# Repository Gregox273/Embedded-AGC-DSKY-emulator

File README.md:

# Embedded-AGC-DSKY-emulator
Apollo Block II AGC + DSKY emulator based on the virtualagc project (https://github.com/virtualagc/virtualagc).
The system is based on an STM32 32-bit ARM Cortex MCU, with custom PCB layout to match the position of buttons and lamps 
on the original DSKY.

### Repository Layout
* **agg-kicad:** submodule by Adam Greig containing useful KiCAD libraries, footprints and scripts.
* **binary_transcoder:** simple C program to rearrange binary output of the yaYUL assembler (see **virtualagc** 
submodule) into the order required for yaAGC emulator (also contained within **virtualagc**). Note that a pre-transcoded
binary file for Luminary099 is provided in the **firmware** directory.
* **ChibiOS:** ChibiOS RTOS submodule, developed by Giovanni Di Sirio.
* **firmware:** directory containing project source code.
* **gen-board.h:** submodule containing Python tool for generating ChibiOS 'board.h' header from a YAML file.
* **pcb:** directory containing project schematics and PCB design:
    * **agc-dsky:** KiCAD schematic and PCB files.
    * **agc-dsky.pretty:** Various component footprints.
    * **lib:** Various schematic symbols.
* **virtualagc:** Virtual Apollo Guidance Computer submodule. Contents include yaYUL (Apollo language assembler) and 
yaAGC (Apollo Guidance Computer emulator).

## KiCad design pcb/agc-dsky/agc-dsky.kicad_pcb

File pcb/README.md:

# Hardware Notes
* STM32F072RBT6 48MHz microcontroller based on ARM Cortex-M0 core. 48MHz appears to be too slow to run the emulator and 
DSKY in realtime...
* MPU9250 IMU present on SPI2 bus (firmware can communicate with device but it has not yet been incorporated into the 
AGC emulation).
* Powered via Micro USB (<500mA current consumption at any time, so can be powered from e.g. a USB port on a computer).
* Microcontroller can be flashed over USB using DFU, or via Serial Wire Debug (SWD).
* TPS62132 switching regulator (5V USB to 3.3V) - high efficiency reduces overall current consumption.
* MCP23S08 SPI I/O expanders used to drive 7 segment displays in a multiplexed array.
  * Three displays are illuminated at a time, striking a balance between brightness and current consumption.
* Push buttons are multiplexed in a key matrix to reduce I/O pin usage.
* WS2812B LEDs arranged in a chain, allowing them to be driven from a single output pin. Each LED internally handles PWM
for red, green and blue channels.
  * Todo: drive LEDs using DMA instead of blocking the processor. This technique appears to be better documented on 
  STM32F3 and STM32F4 microcontrollers.
* UART port exposed (2.54mm header) to allow for future modifications/experimentation.

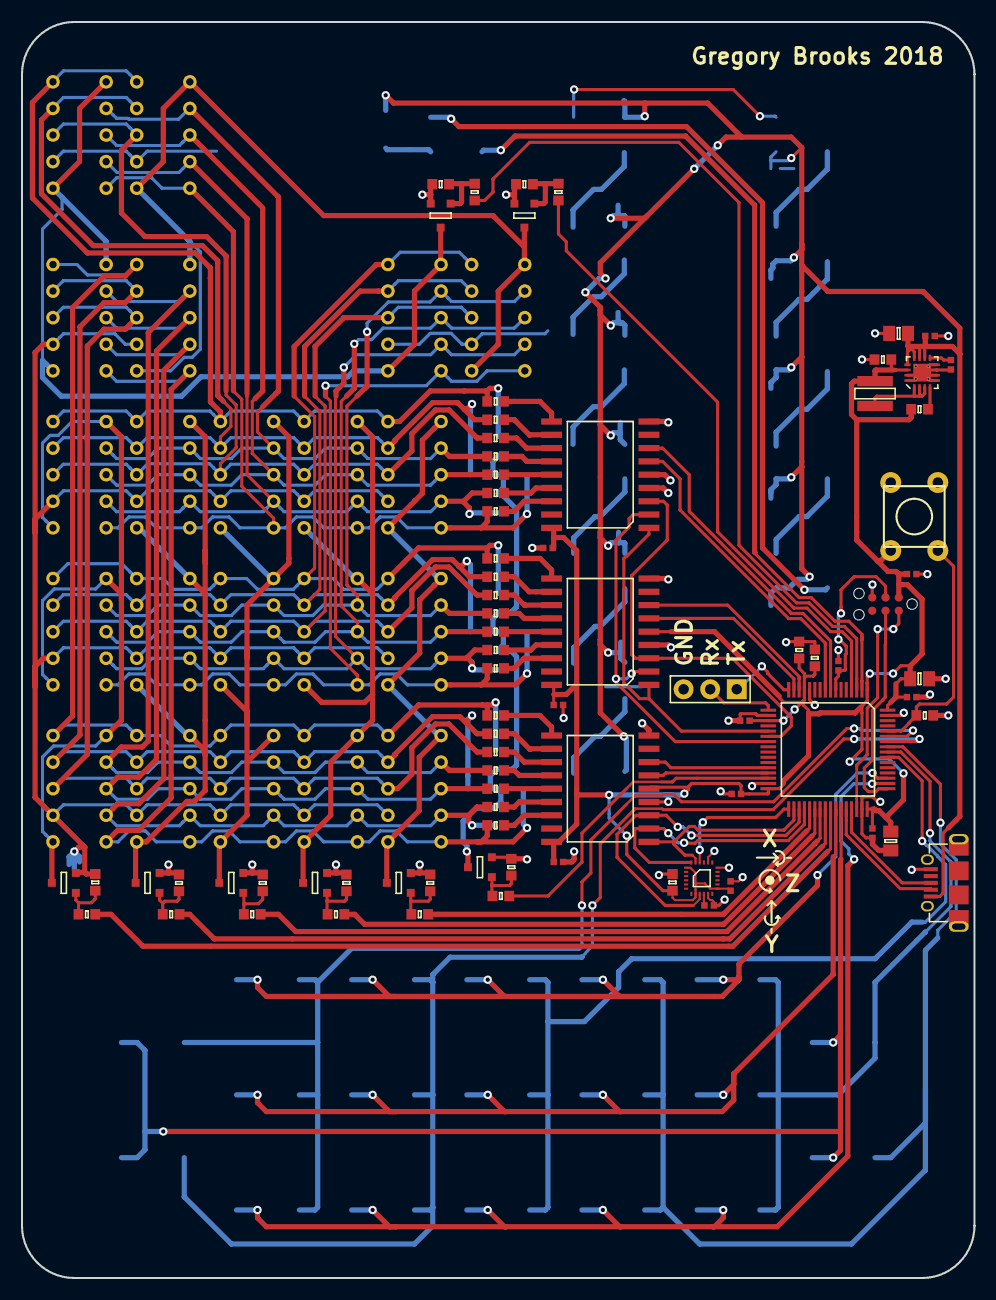
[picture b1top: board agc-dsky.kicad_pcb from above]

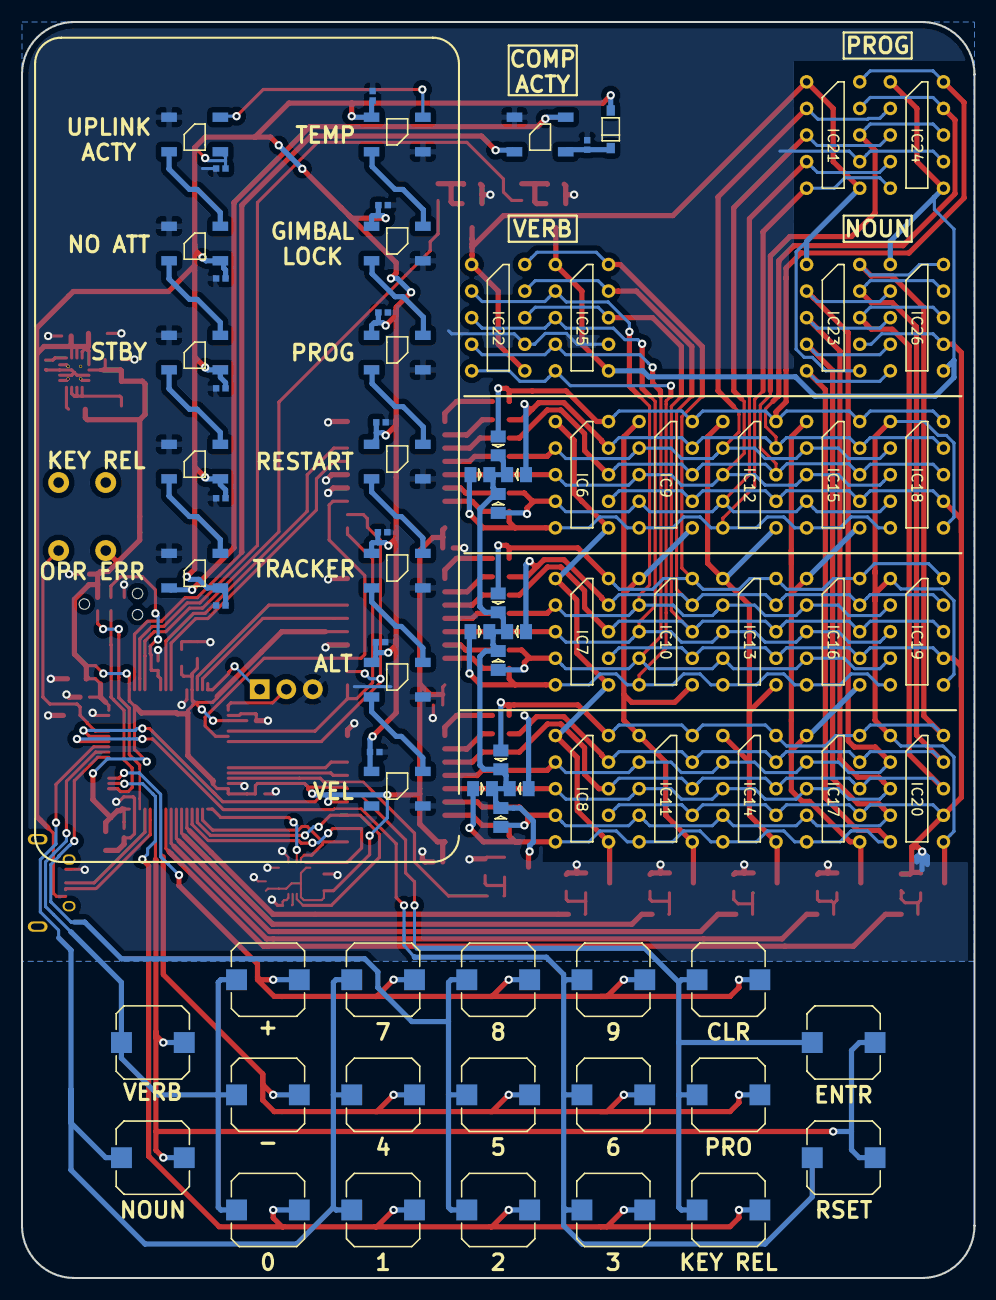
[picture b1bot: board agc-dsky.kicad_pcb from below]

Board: 2 copper layers, 91.0 x 120.0 mm, 157 parts (79 on the bottom side), 117 nets.

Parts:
C1: 10uF; 0805
C2, C4, C7, C10, C11, C13, C14, C15, C16, C17, C18, C19, C20, C21, C22, C23, C24, C25, C26, C27, C28, C29, C30, C31, C33: 100nF; 0402
C3: 3.3nF; 0402
C5: 22uF; 0603
C6, C8: 4.7uF; 0805
C9: 1uF; 0603
C12, C32: 10nF; 0603
D1, D2, D3, D4, D5, D6, D7, D8, D9, D10, D11, D12: LED; 0805-LED
D13: MMSD4148T1G; SOD-123
IC1: TPS62132; QFN-16-EP-TI
IC2: STM32F072RBT6; LQFP-64
IC3, IC4, IC5: MCP23S08; SOIC-18-W
IC6, IC7, IC8, IC9, IC10, IC11, IC12, IC13, IC14, IC15, IC16, IC17, IC18, IC19, IC20, IC21, IC22, IC23, IC24, IC25, IC26: LDS-3161AX
IC27, IC28, IC29, IC30, IC31, IC32, IC33, IC34, IC35, IC36, IC37, IC38, IC39: WS2812B
IC40: MPU-9250; QFN-24-MPU9250
J1: MICROUSB; MICROUSB_MOLEX_47589-0001
J2: CONN_01x03; SIL-254P-03
L1: 2.2uH; XFL4020
P1: SWD_TC; TC2030-NL
Q1, Q2, Q3, Q4, Q5, Q6, Q7, Q8: FDN327N; supersot-3
R1, R2: 100k; 0603
R3, R4, R5, R6, R7, R8, R9, R10, R11, R12, R13, R14, R15, R16, R17, R18, R19, R20, R21, R22, R23, R24, R26, R28, R30, R32, R34, R36, R38: 100; 0603
R25, R27, R29, R31, R33, R35, R37, R39: 1M; 0603
SW1, SW2, SW3, SW4, SW5, SW6, SW7, SW8, SW10, SW11, SW12, SW13, SW14, SW15, SW16, SW17, SW18, SW19, SW20: SKPMAME010; SKPM
SW9: SKHHALA010; MOM_SWITCH

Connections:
3v3: C4.1, C5.1, C6.1, C7.1, C8.1, C9.1, C10.1, C11.1, C12.1, C13.1, C15.1, C16.1, C17.1, C31.2, C32.1, IC1.14, IC2.1, IC2.13, IC2.19, IC2.32, IC2.48, IC2.64, IC3.18, IC4.5, IC4.18, IC5.4, IC5.5, IC5.18, IC40.1, IC40.8, IC40.13, L1.2, P1.1, R1.1, SW9.2
5v: C1.1, C2.1, C18.1, C19.1, C20.1, C21.1, C22.1, C24.1, C25.1, C26.1, C27.1, C28.1, C29.1, C30.1, D13.2, IC1.10, IC1.11, IC1.12, IC1.13, IC28.1, IC29.1, IC30.1, IC31.1, IC32.1, IC33.1, IC34.1, IC35.1, IC36.1, IC37.1, IC38.1, IC39.1, J1.1
/7-segs/A1: D10.2, IC6.10, IC9.10, IC12.10, IC15.10, IC18.10, IC21.10, IC24.10, R15.2
/7-segs/A2: D11.2, IC7.10, IC10.10, IC13.10, IC16.10, IC19.10, IC22.10, IC25.10, R18.2
/7-segs/A3: D12.2, IC8.10, IC11.10, IC14.10, IC17.10, IC20.10, IC23.10, IC26.10, R21.2
/7-segs/B1: D7.2, IC6.9, IC9.9, IC12.9, IC15.9, IC18.9, IC21.9, IC24.9, R9.2
/7-segs/B2: D8.2, IC7.9, IC10.9, IC13.9, IC16.9, IC19.9, IC22.9, IC25.9, R11.2
/7-segs/B3: D9.2, IC8.9, IC11.9, IC14.9, IC17.9, IC20.9, IC23.9, IC26.9, R13.2
/7-segs/C1: IC6.8, IC9.8, IC12.8, IC15.8, IC18.8, IC21.8, IC24.8, R3.2
/7-segs/C2: IC7.8, IC10.8, IC13.8, IC16.8, IC19.8, IC22.8, IC25.8, R5.2
/7-segs/C3: IC8.8, IC11.8, IC14.8, IC17.8, IC20.8, IC23.8, IC26.8, R7.2
/7-segs/D1: D4.2, IC6.5, IC9.5, IC12.5, IC15.5, IC18.5, IC21.5, IC24.5, R17.2
/7-segs/D2: D5.2, IC7.5, IC10.5, IC13.5, IC16.5, IC19.5, IC22.5, IC25.5, R20.2
/7-segs/D3: D6.2, IC8.5, IC11.5, IC14.5, IC17.5, IC20.5, IC23.5, IC26.5, R23.2
/7-segs/E1: D1.2, IC6.4, IC9.4, IC12.4, IC15.4, IC18.4, IC21.4, IC24.4, R4.2
/7-segs/E2: D2.2, IC7.4, IC10.4, IC13.4, IC16.4, IC19.4, IC22.4, IC25.4, R6.2
/7-segs/E3: D3.2, IC8.4, IC11.4, IC14.4, IC17.4, IC20.4, IC23.4, IC26.4, R8.2
/7-segs/F1: IC6.2, IC9.2, IC12.2, IC15.2, IC18.2, IC21.2, IC24.2, R16.2
/7-segs/F2: IC7.2, IC10.2, IC13.2, IC16.2, IC19.2, IC22.2, IC25.2, R19.2
/7-segs/F3: IC8.2, IC11.2, IC14.2, IC17.2, IC20.2, IC23.2, IC26.2, R22.2
/7-segs/G1: IC6.3, IC9.3, IC12.3, IC15.3, IC18.3, IC21.3, IC24.3, R10.2
/7-segs/G2: IC7.3, IC10.3, IC13.3, IC16.3, IC19.3, IC22.3, IC25.3, R12.2
/7-segs/G3: IC8.3, IC11.3, IC14.3, IC17.3, IC20.3, IC23.3, IC26.3, R14.2
/BC1: IC2.56, SW1.1, SW2.1, SW3.1, SW4.1
/BC2: IC2.57, SW5.1, SW6.1, SW7.1, SW8.1
/BC3: IC2.55, SW10.1, SW11.1, SW12.1
/BC4: IC2.58, SW14.1, SW15.1, SW16.1, SW17.1
/BC5: IC2.59, SW13.1, SW18.1, SW19.1, SW20.1
/BR1: IC2.51, SW1.2, SW5.2, SW10.2, SW14.2, SW18.2
/BR2: IC2.42, SW2.2, SW6.2, SW11.2, SW15.2, SW19.2
/BR3: IC2.50, SW3.2, SW7.2, SW12.2, SW16.2, SW20.2
/BR4: IC2.43, SW4.2, SW8.2, SW13.2, SW17.2
/Co1: IC2.37, R24.1
/Co2: IC2.38, R26.1
/Co3: IC2.39, R28.1
/Co4: IC2.40, R30.1
/Co5: IC2.41, R32.1
/Co6: IC2.4, R34.1
/Co7: IC2.3, R36.1
/Co8: IC2.30, R38.1
/LED_DIN: IC2.2, IC27.4
/NCS_1: IC2.8, IC3.7
/NCS_2: IC2.14, IC4.7
/NCS_3: IC2.28, IC5.7
/NCS_MPU: IC2.33, IC40.22
/NRST: C14.1, IC2.7, P1.3
/NRST_1: IC2.9, IC3.6
/NRST_2: IC2.15, IC4.6
/NRST_3: IC2.29, IC5.6
/SPI1_SCK: IC2.21, IC3.1, IC4.1
/SPI1_SI: IC2.23, IC3.2, IC4.2
/SPI1_SO: IC2.22, IC3.3, IC4.3
/SPI2_SCK: IC2.34, IC5.1, IC40.23
/SPI2_SI: IC2.36, IC5.2, IC40.24
/SPI2_SO: IC2.35, IC5.3, IC40.9
/SWDCLK: IC2.49, P1.4
/SWDIO: IC2.46, P1.2
GND: C1.2, C2.2, C3.1, C4.2, C5.2, C6.2, C7.2, C8.2, C9.2, C10.2, C11.2, C12.2, C13.2, C14.2, C15.2, C16.2, C17.2, C18.2, C19.2, C20.2, C21.2, C22.2, C23.2, C24.2, C25.2, C26.2, C27.2, C28.2, C29.2, C30.2, C31.1, C32.2, C33.2, IC1.5, IC1.6, IC1.7, IC1.8, IC1.15, IC1.16, IC1.EP, IC2.12, IC2.18, IC2.31, IC2.47, IC2.63, IC3.4, IC3.5, IC3.9, IC4.4, IC4.9, IC5.9, IC6.7, IC7.7, IC8.7, IC9.7, IC10.7, IC11.7, IC12.7, IC13.7, IC14.7, IC15.7, IC16.7, IC17.7, IC18.7, IC19.7, IC20.7, IC21.7, IC22.7, IC23.7, IC24.7, IC25.7, IC26.7, IC27.3, IC28.3, IC29.3, IC30.3, IC31.3, IC32.3, IC33.3, IC34.3, IC35.3, IC36.3, IC37.3, IC38.3, IC39.3, IC40.11, IC40.18, IC40.20, J1.5, J2.3, P1.5, Q1.S, Q2.S, Q3.S, Q4.S, Q5.S, Q6.S, Q7.S, Q8.S, R2.2, R25.2, R27.2, R29.2, R31.2, R33.2, R35.2, R37.2, R39.2
unnamed: C3.2, IC1.9
unnamed: C23.1, D13.1, IC27.1
unnamed: C33.1, IC40.10
unnamed: D1.1, D2.1, D3.1, D4.1, D5.1, D6.1, D7.1, D8.1, D9.1, D10.1, D11.1, D12.1, Q8.D
unnamed: IC1.1, IC1.2, IC1.3, L1.1
unnamed: IC1.4, R1.2
unnamed: IC2.16, J2.1
unnamed: IC2.17, J2.2
unnamed: IC2.44, J1.2
unnamed: IC2.45, J1.3
unnamed: IC2.60, R2.1, SW9.1
unnamed: IC3.10, R15.1
unnamed: IC3.11, R9.1
unnamed: IC3.12, R3.1
unnamed: IC3.13, R16.1
unnamed: IC3.14, R10.1
unnamed: IC3.15, R4.1
unnamed: IC3.16, R17.1
unnamed: IC4.10, R18.1
unnamed: IC4.11, R11.1
unnamed: IC4.12, R5.1
unnamed: IC4.13, R19.1
unnamed: IC4.14, R12.1
unnamed: IC4.15, R6.1
unnamed: IC4.16, R20.1
unnamed: IC5.10, R21.1
unnamed: IC5.11, R13.1
unnamed: IC5.12, R7.1
unnamed: IC5.13, R22.1
unnamed: IC5.14, R14.1
unnamed: IC5.15, R8.1
unnamed: IC5.16, R23.1
unnamed: IC6.1, IC6.6, IC7.1, IC7.6, IC8.1, IC8.6, Q1.D
unnamed: IC9.1, IC9.6, IC10.1, IC10.6, IC11.1, IC11.6, Q2.D
unnamed: IC12.1, IC12.6, IC13.1, IC13.6, IC14.1, IC14.6, Q3.D
unnamed: IC15.1, IC15.6, IC16.1, IC16.6, IC17.1, IC17.6, Q4.D
unnamed: IC18.1, IC18.6, IC19.1, IC19.6, IC20.1, IC20.6, Q5.D
unnamed: IC21.1, IC21.6, IC22.1, IC22.6, IC23.1, IC23.6, Q6.D
unnamed: IC24.1, IC24.6, IC25.1, IC25.6, IC26.1, IC26.6, Q7.D
unnamed: IC27.2, IC28.4
unnamed: IC28.2, IC29.4
unnamed: IC29.2, IC30.4
unnamed: IC30.2, IC31.4
unnamed: IC31.2, IC32.4
unnamed: IC32.2, IC33.4
unnamed: IC33.2, IC34.4
unnamed: IC34.2, IC35.4
unnamed: IC35.2, IC36.4
unnamed: IC36.2, IC37.4
unnamed: IC37.2, IC38.4
unnamed: IC38.2, IC39.4
unnamed: Q1.G, R24.2, R25.1
unnamed: Q2.G, R26.2, R27.1
unnamed: Q3.G, R28.2, R29.1
unnamed: Q4.G, R30.2, R31.1
unnamed: Q5.G, R32.2, R33.1
unnamed: Q6.G, R34.2, R35.1
unnamed: Q7.G, R36.2, R37.1
unnamed: Q8.G, R38.2, R39.1

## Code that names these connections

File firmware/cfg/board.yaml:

name: AGC/DSKY Emulator
lsefreq: 0
hsefreq: 0
voltage: 3.3
mcutype: STM32F072xB
other:
    STM32_HSE_BYPASS: ~
    STM32_LSEDRV: (3U << 3U) 
default: input, pushpull, starthigh, pullup, highspeed
pins:
    usb_dm : pa11, af0
    usb_dp : pa12, af0
    swdio  : pa13, af0
    swclk  : pa14, af0, pulldown
    led_din: pc13, output, startlow, floating
    
    ncs_1: pc0, output, floating
    ncs_2: pa0, output, floating
    ncs_3: pb2, output, floating
    
    nrst_1: pc1, output, floating
    nrst_2: pa1, output, floating
    nrst_3: pb10, output, floating
    
    usart_tx: pa2, af1, floating
    usart_rx: pa3, af1, floating
    
    spi1_sck : pa5, af0, floating
    spi1_miso: pa6, af0, floating
    spi1_mosi: pa7, af0, floating
    ncs_mpu  : pb12, output, floating
    spi2_sck : pb13, af0, floating
    spi2_miso: pb14, af0, floating
    spi2_mosi: pb15, af0, floating
    
    co1: pc6, output, startlow, floating
    co2: pc7, output, startlow, floating
    co3: pc8, output, startlow, floating
    co4: pc9, output, startlow, floating
    co5: pa8, output, startlow, floating
    co6: pc15, output, startlow, floating
    co7: pc14, output, startlow, floating
    co8: pb11, output, startlow, floating
    
    br1: pc10, output, startlow, floating
    br2: pa9, output, startlow, floating
    br3: pa15, output, startlow, floating
    br4: pa10, output, startlow, floating
    
    bc1: pb4, pulldown
    bc2: pb5, pulldown
    bc3: pb3, pulldown
    bc4: pb6, pulldown
    bc5: pb7, pulldown

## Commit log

2018-11-04 Add submodules and set up ChibiOS project from example for STM32F072RBT6
2018-11-05 Begin configuring ChibiOS and add virtualagc fork as submodule
2018-11-07 Add buttons to schematic
2018-11-07 Add STM32F072RBT6 symbol
2018-11-08 Work on 7 segment displays
2018-11-09 Add MCP23S08 I/O expander symbol
2018-11-09 Add SOIC-18-W footprint
2018-11-10 First revision of schematic
2018-11-10 Replace 14 segment displays with discrete LEDs and rearrange display driver system
2018-11-10 Progress with DSKY board layout
2018-11-10 Work on routing displays
2018-11-10 More work on routing displays
2018-11-10 Add ground pour on bottom layer
2018-11-11 More work on layout
2018-11-11 More routing of buttons
2018-11-11 First routing attempt
2018-11-11 First attempt at routing complete
2018-11-11 Add BOM and stickers
2018-11-11 Bridge separated ground plane through ALT LED and add name + date to silkscreen
2018-11-11 Thicken power traces
2018-11-12 Tidy up button references
2018-11-12 Add UART header and imu
2018-11-12 Generate gerbers
2018-11-12 Modify gerber filenames & create zip for dirtypcbs
2018-11-12 Save pcb with gerber info
2018-11-12 Remove drill map
2018-11-29 Fix mistakes in BOM
2018-12-05 Set up board config and update makefile with custom commands
2018-12-06 Add schematic Pdf and update sticker pdf
2018-12-08 Add some yaagc files and first attempt at key matrix driver
2018-12-09 Begin porting over MPU9250 driver from CUSF spalax
2018-12-29 Update buttons driver to signal changes in button state
2018-12-30 Work on buttons & display drivers
2018-12-30 Bug fixes for display & buttons drivers
2018-12-30 Update test functions and document work so far
2018-12-30 Add third party ws2812 driver, reduce clock speed to 24MHz to allow zero wait state for accurate timing
2018-12-31 Update ws2812 driver and add lamps driver
2018-12-31 Update test sequence and add code to handle plus/minus when setting displays
2018-12-31 Add chDbgAssert() to verify function inputs
2019-01-01 Fix bugs for display & button threads working in parallel
2019-01-01 Work on lamp driver
2019-01-01 Attempt at DMA ws2812 driver
2019-01-02 Attempt a simplified DMA driver (not working)
2019-01-02 First revision of working blocking WS2812B driver
2019-01-03 Add to lamps driver and begin integrating yaAGC
2019-01-04 More work on porting yaAGC
2019-01-05 Work on yaAGC channel interface (NullAPI)
2019-01-05 First working lamp test
2019-01-05 Small bugfixes and optimisations
2019-01-07 Update README files
2019-01-07 Fix verb/noun flash bug
2019-01-07 mpu9250 driver appears to work
2019-01-07 Add hardware README
2019-01-07 Tidy up code
2019-01-15 More work on mpu9250 demo
